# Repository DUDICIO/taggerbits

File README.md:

# taggerbits
An arduino based prototyping board with RFID and wifi capability on single PCB.

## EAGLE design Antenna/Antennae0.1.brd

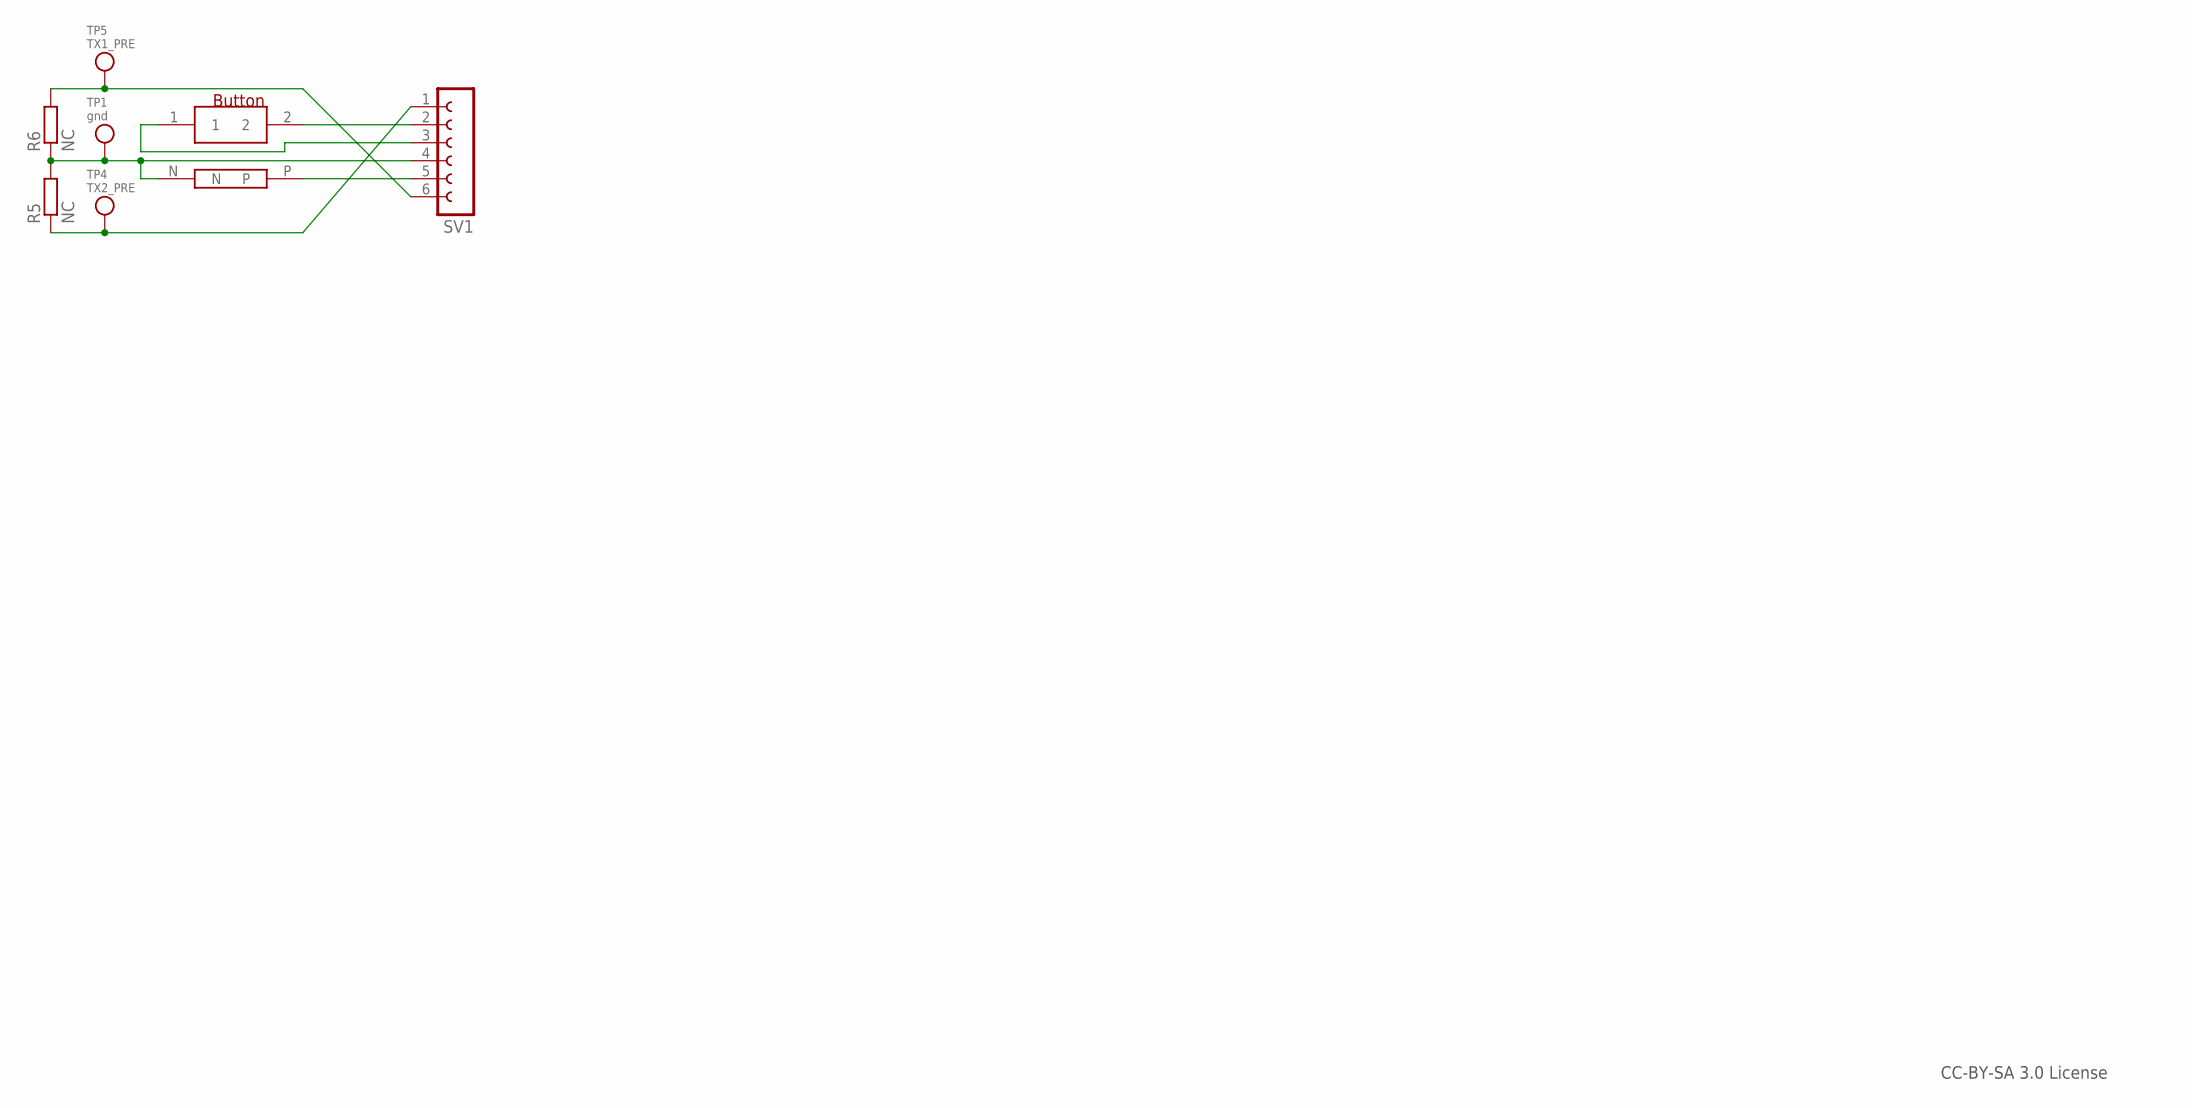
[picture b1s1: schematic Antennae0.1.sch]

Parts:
R5, R6: NC; R0201
SV1: FE06-1; FE06
TP1: gnd; TESTPOINT_PAD_2MM
TP4: TX2_PRE; TESTPOINT_PAD_2MM
TP5: TX1_PRE; TESTPOINT_PAD_2MM
U$1: BUTTON
U$2: LED(805)

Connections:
unnamed: SV1.2, U$1.2
unnamed: SV1.5, U$2.P
unnamed: R6.2, SV1.6, TP5.P$1
unnamed: R5.1, SV1.1, TP4.P$1
unnamed: R5.2, R6.1, SV1.4, TP1.P$1, U$2.N
VCC: SV1.3, U$1.1

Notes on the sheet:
CC-BY-SA 3.0 License

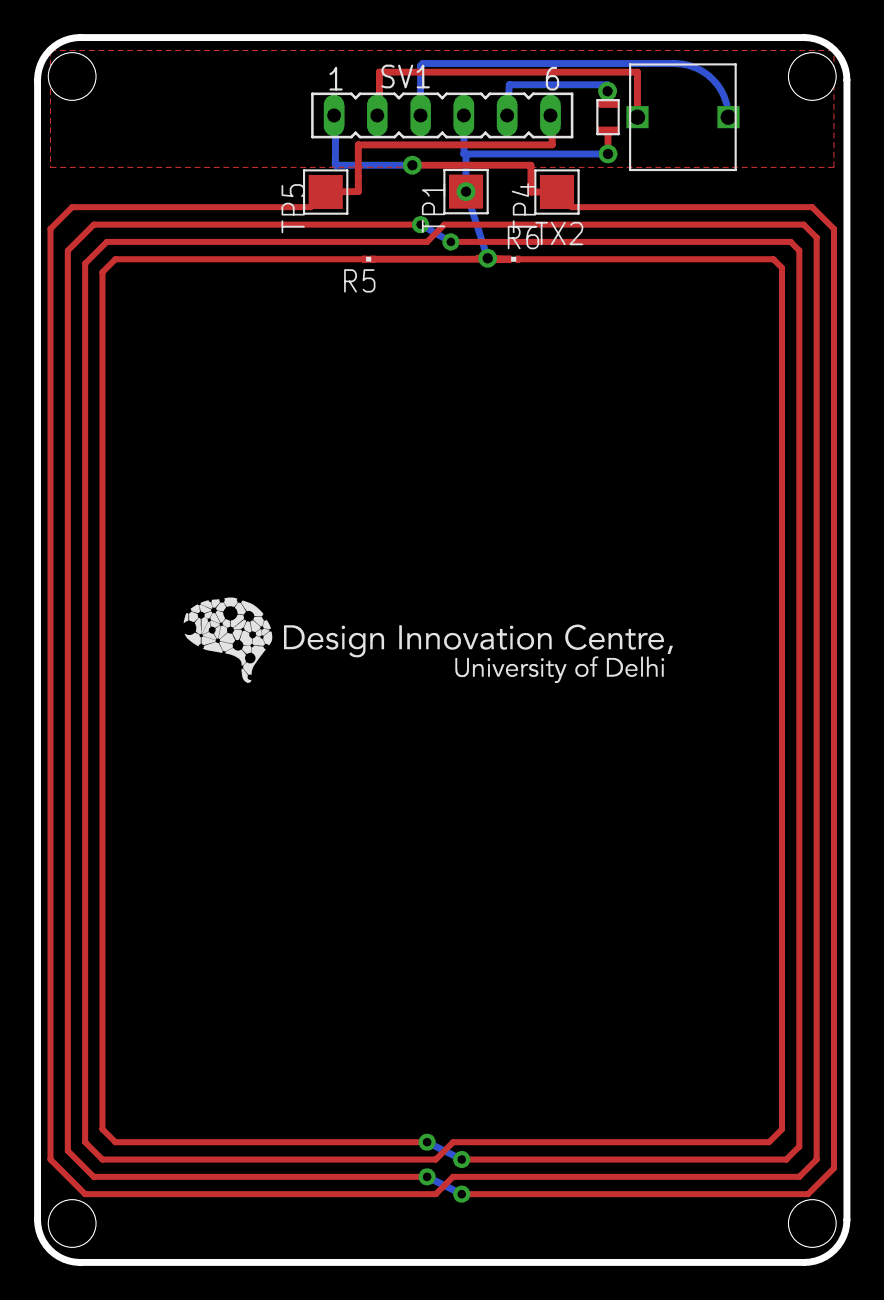
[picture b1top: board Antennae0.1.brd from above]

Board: 2 copper layers, 47.5 x 71.9 mm, 8 parts (0 on the bottom side), 6 nets.

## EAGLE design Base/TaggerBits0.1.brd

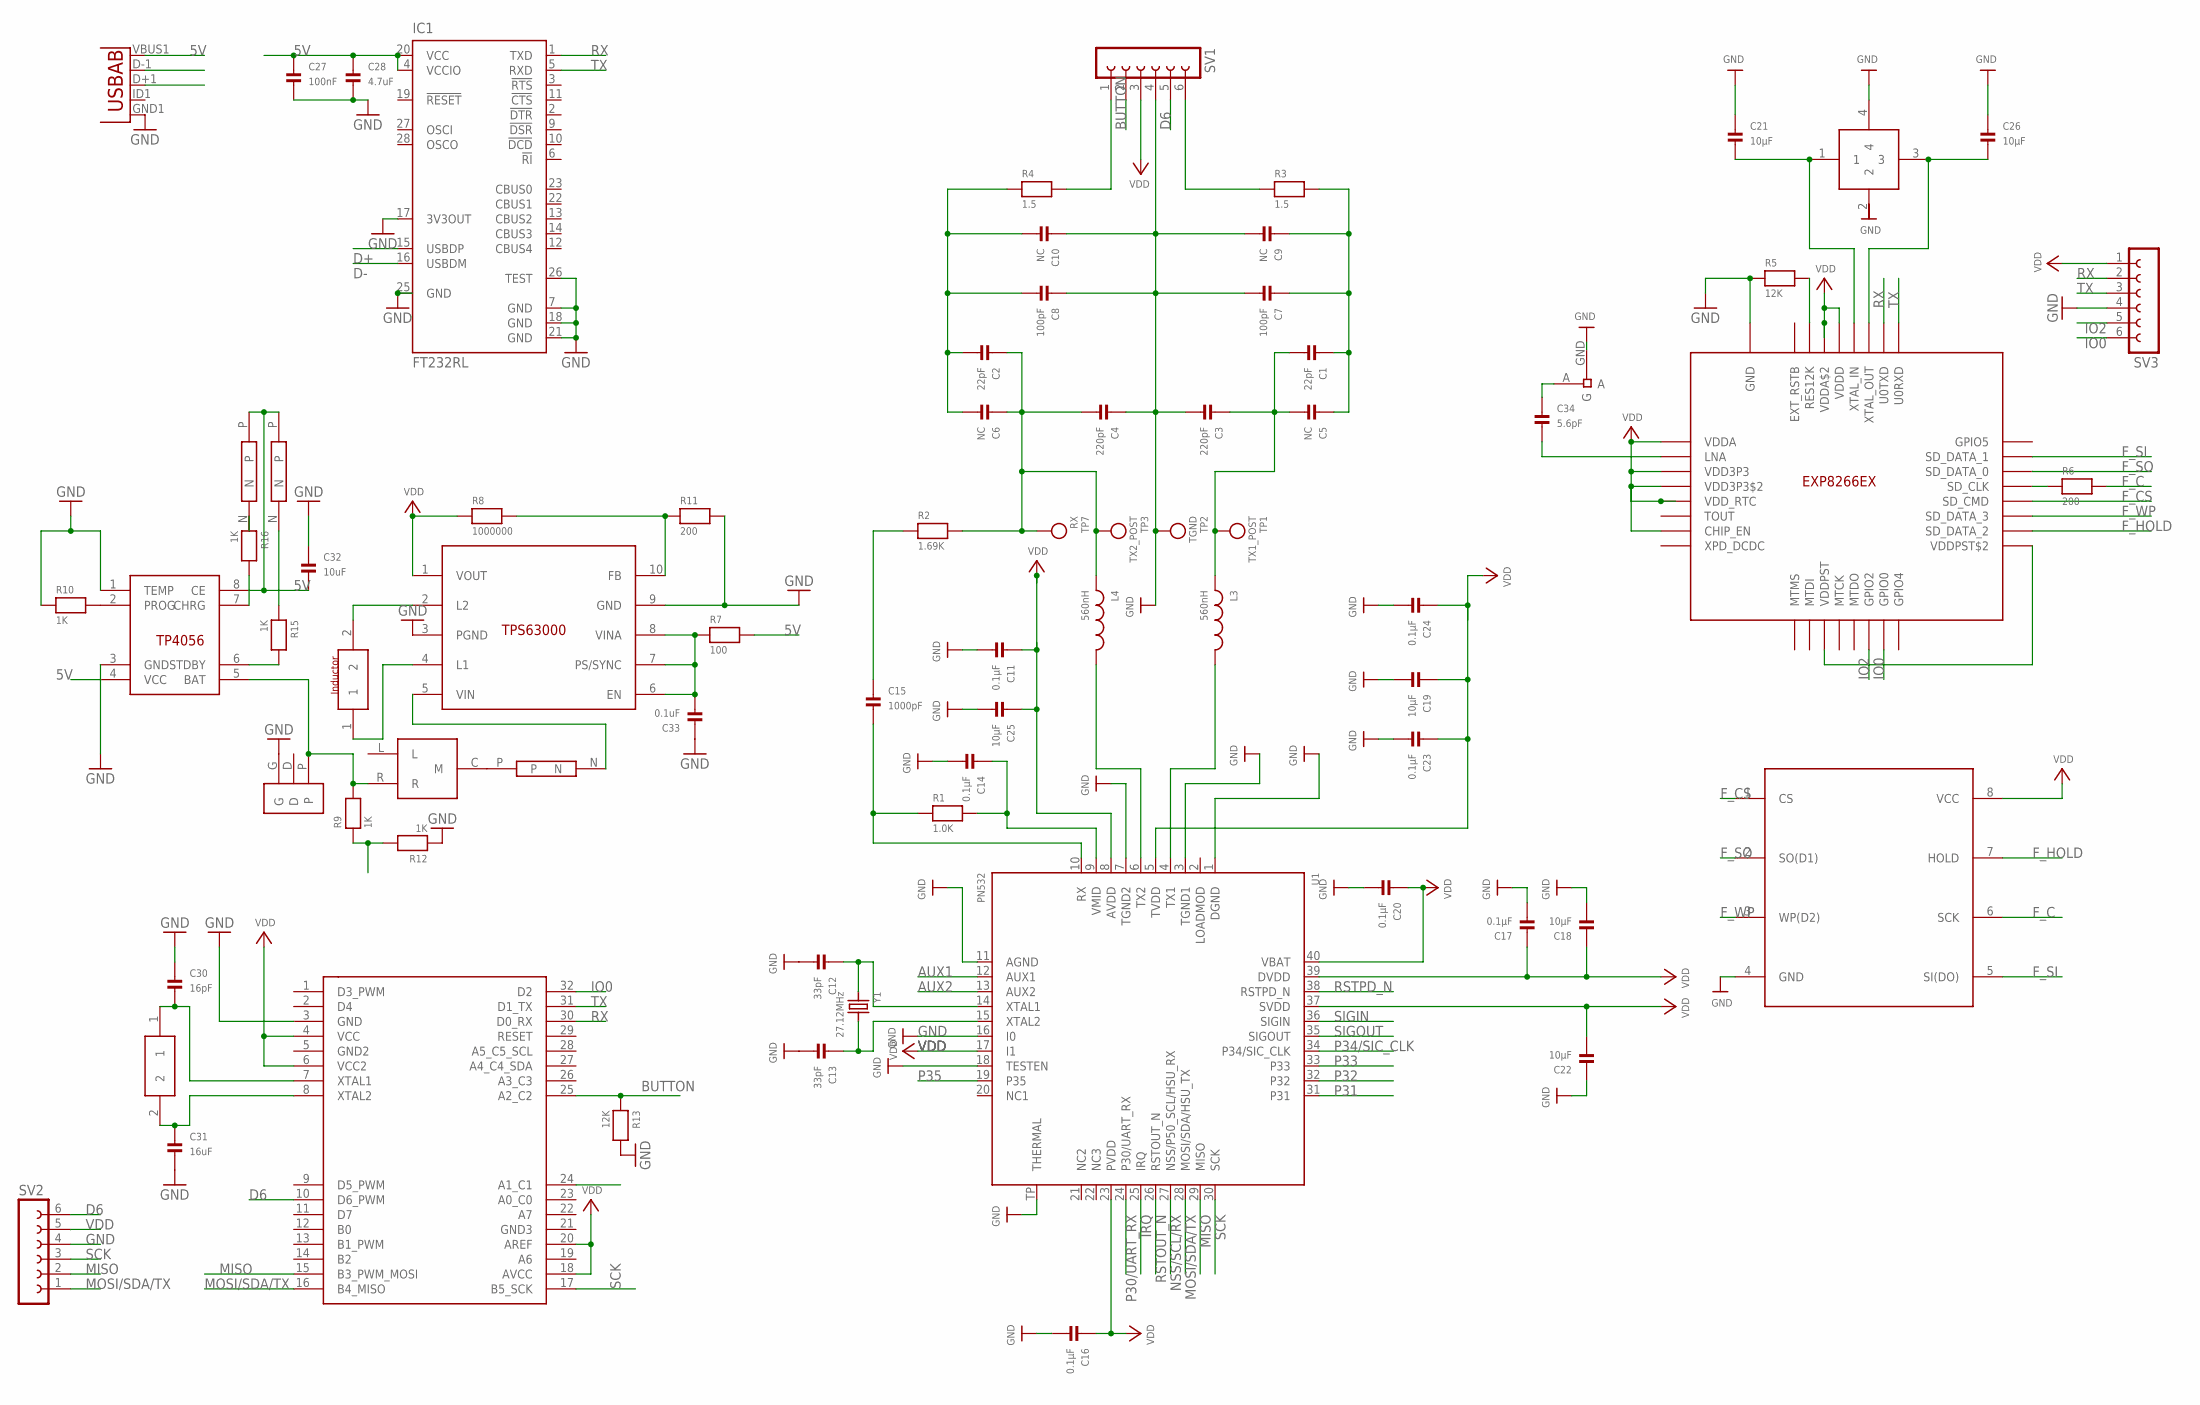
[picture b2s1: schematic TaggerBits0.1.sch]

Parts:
C1, C2: 22pF; 0805
C3, C4: 220pF; 0805
C5, C6, C9, C10: NC; 0805
C7, C8: 100pF; 0805
C11, C14, C16, C17, C20, C23, C24: 0.1µF; 0805
C12, C13: 33pF; 0805
C15: 1000pF; 0805
C18, C19, C21, C22, C25, C26: 10µF; 0805
C27: 100nF; 0805
C28: 4.7uF; 0805
C30: 16pF; 0805
C31: 16uF; 0805
C32: 10uF; 0805
C33: 0.1uF; 0805
C34: 5.6pF; 0805
GREEN: LED(805)
IC1: FT232RL; SSOP28
L3, L4: 560nH; 0805
LED: LED(805)
R1: 1.0K; 0805
R2: 1.69K; 0805
R3, R4: 1.5; 0805
R5, R13: 12K; 0805
R6, R11: 200; 0805
R7: 100; 0805
R8: 1000000; 0805
R9, R10, R12, R15, R16: 1K; 0805
RED: LED(805)
SV1, SV2, SV3: FE06-1; FE06
TP1: TX1_POST; TESTPOINT_PAD_2MM
TP2: TGND; TESTPOINT_PAD_2MM
TP3: TX2_POST; TESTPOINT_PAD_2MM
TP7: RX; TESTPOINT_PAD_2MM
U1: PN532; HVQFN40-6X6
U3: USB""; USB-MICRO-SMD
U4: ESP8266EX
U$3: FLASH; SO08
U$6: ATMEGA328TQFP; TQFP32-08
U$31: ANTENNAE
U$33: 26MHZ; T120
U$41: TP4056; SO08
U$42: CRYSTAL
U$44: TPS63000; SON10
U$47: SPDT
U$48: BCON
U$49: INDUCTOR
Y1: 27.12MHz; CRYSTAL_3.2X2.5

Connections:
5V: C27.1, C28.1, C32.2, GREEN.P, IC1.4 (VCCIO), IC1.20 (VCC), R7.2, RED.P, U3.VBUS1 (VBUS), U$41.4 (VCC), U$41.8 (CE)
AUX1: U1.12 (AUX1)
AUX2: U1.13 (AUX2)
BATTERYI: R9.1, R12.2, U$6.24 (A1_C1)
BUTTON: R13.1, SV1.2, U$6.25 (A2_C2)
D6: SV1.5, SV2.6, U$6.10 (D6_PWM)
D+: IC1.15 (USBDP), U3.D+1 (D+)
D-: IC1.16 (USBDM), U3.D-1 (D-)
F_C: R6.2, U$3.6 (SCK)
F_CS: U4.SD_CMD, U$3.1 (CS)
F_HOLD: U4.SD_DATA_2, U$3.7 (HOLD)
F_SI: U4.SD_DATA_1, U$3.5 (SI(DO))
F_SO: U4.SD_DATA_0, U$3.2 (SO(D1))
F_WP: U4.SD_DATA_3, U$3.3 (WP(D2))
GND: C3.2, C4.1, C7.2, C8.1, C9.2, C10.1, C11.2, C12.2, C13.2, C14.2, C16.2, C17.2, C18.2, C19.2, C20.2, C21.1, C22.1, C23.2, C24.2, C25.2, C26.1, C27.2, C28.2, C30.1, C31.2, C32.1, C33.1, IC1.7 (GND), IC1.17 (3V3OUT), IC1.18 (GND), IC1.21 (GND), IC1.25 (GND), IC1.26 (TEST), R5.1, R10.1, R11.2, R12.1, R13.2, SV1.4, SV2.4, SV3.4, TP2.P$1, U1.1 (DGND), U1.3 (TGND1), U1.7 (TGND2), U1.11 (AGND), U1.16 (I0), U1.18 (TESTEN), U1.TP (THERMAL), U3.GND1 (GND), U4.GND, U$3.4 (GND), U$6.3 (GND), U$31.GND (G), U$33.4, U$41.1 (TEMP), U$41.3 (GND), U$44.3 (PGND), U$44.9 (GND), U$48.G
IO0: SV3.6, U4.GPIO0, U$6.32 (D2)
IO2: SV3.5, U4.GPIO2
IRQ: U1.25 (IRQ)
MISO: SV2.2, U1.29 (MISO), U$6.15 (B3_PWM_MOSI)
MOSI/SDA/TX: SV2.1, U1.28 (MOSI/SDA/HSU_TX), U$6.16 (B4_MISO)
unnamed: L3.2, U1.4 (TX1)
unnamed: L4.2, U1.6 (TX2)
unnamed: C1.2, C3.1, C5.2, L3.1, TP1.P$1
unnamed: R3.1, SV1.6
unnamed: R4.2, SV1.1
unnamed: C34.2, U4.LNA
unnamed: C12.1, U1.14 (XTAL1), Y1.1
unnamed: C13.1, U1.15 (XTAL2), Y1.2
unnamed: C15.1, R2.1
unnamed: C14.1, R1.2, U1.9 (VMID)
unnamed: C15.2, R1.1, U1.10 (RX)
unnamed: C2.1, C4.2, C6.1, L4.1, R2.2, TP3.P$1, TP7.P$1
unnamed: LED.N, U$44.5 (VIN)
unnamed: C21.2, U4.XTAL_IN, U$33.1
unnamed: C30.2, U$6.7 (XTAL1), U$42.1
unnamed: C31.1, U$6.8 (XTAL2), U$42.2
unnamed: C33.2, R7.1, U$44.6 (EN), U$44.7 (PS/SYNC), U$44.8 (VINA)
unnamed: R8.2, R11.1, U$44.10 (FB)
unnamed: R5.2, U4.RES12K
unnamed: R6.1, U4.SD_CLK
unnamed: C26.2, U4.XTAL_OUT, U$33.3
unnamed: U4.VDDPST, U4.VDDPST$2
unnamed: R10.2, U$41.2 (PROG)
unnamed: R9.2, U$41.5 (BAT), U$47.R, U$48.P
unnamed: LED.P, U$47.C (M)
unnamed: U$44.4 (L1), U$49.1
unnamed: U$44.2 (L2), U$49.2
unnamed: C34.1, U$31.A
unnamed: R15.2, U$41.6 (STDBY)
unnamed: R16.2, U$41.7 (CHRG)
unnamed: GREEN.N, R15.1
unnamed: R16.1, RED.N
NSS/SCL/RX: U1.27 (NSS/P50_SCL/HSU_RX)
P30/UART_RX: U1.24 (P30/UART_RX)
P31: U1.31
P32: U1.32
P33: U1.33
P34/SIC_CLK: U1.34 (P34/SIC_CLK)
P35: U1.19 (P35)
RSTOUT_N: U1.26 (RSTOUT_N)
RSTPD_N: U1.38 (RSTPD_N)
RX: IC1.1 (TXD), SV3.2, U4.U0TXD, U$6.30 (D0_RX)
SCK: SV2.3, U1.30 (SCK), U$6.17 (B5_SCK)
SIGIN: U1.36 (SIGIN)
SIGOUT: U1.35 (SIGOUT)
TX: IC1.5 (RXD), SV3.3, U4.U0RXD, U$6.31 (D1_TX)
TX1_ANTENNA: C1.1, C5.1, C7.1, C9.1, R3.2
TX2_ANTENNA: C2.2, C6.2, C8.2, C10.2, R4.1
VDD: C11.1, C16.1, C17.1, C18.1, C19.1, C20.1, C22.2, C23.1, C24.1, C25.1, R8.1, SV1.3, SV2.5, SV3.1, U1.5 (TVDD), U1.8 (AVDD), U1.17 (I1), U1.23 (PVDD), U1.37 (SVDD), U1.39 (DVDD), U1.40 (VBAT), U4.CHIP_EN, U4.VDD3P3, U4.VDD3P3$2, U4.VDDA, U4.VDDA$2, U4.VDDD, U4.VDD_RTC, U$3.8 (VCC), U$6.4 (VCC), U$6.6 (VCC2), U$6.18 (AVCC), U$6.20 (AREF), U$44.1 (VOUT)

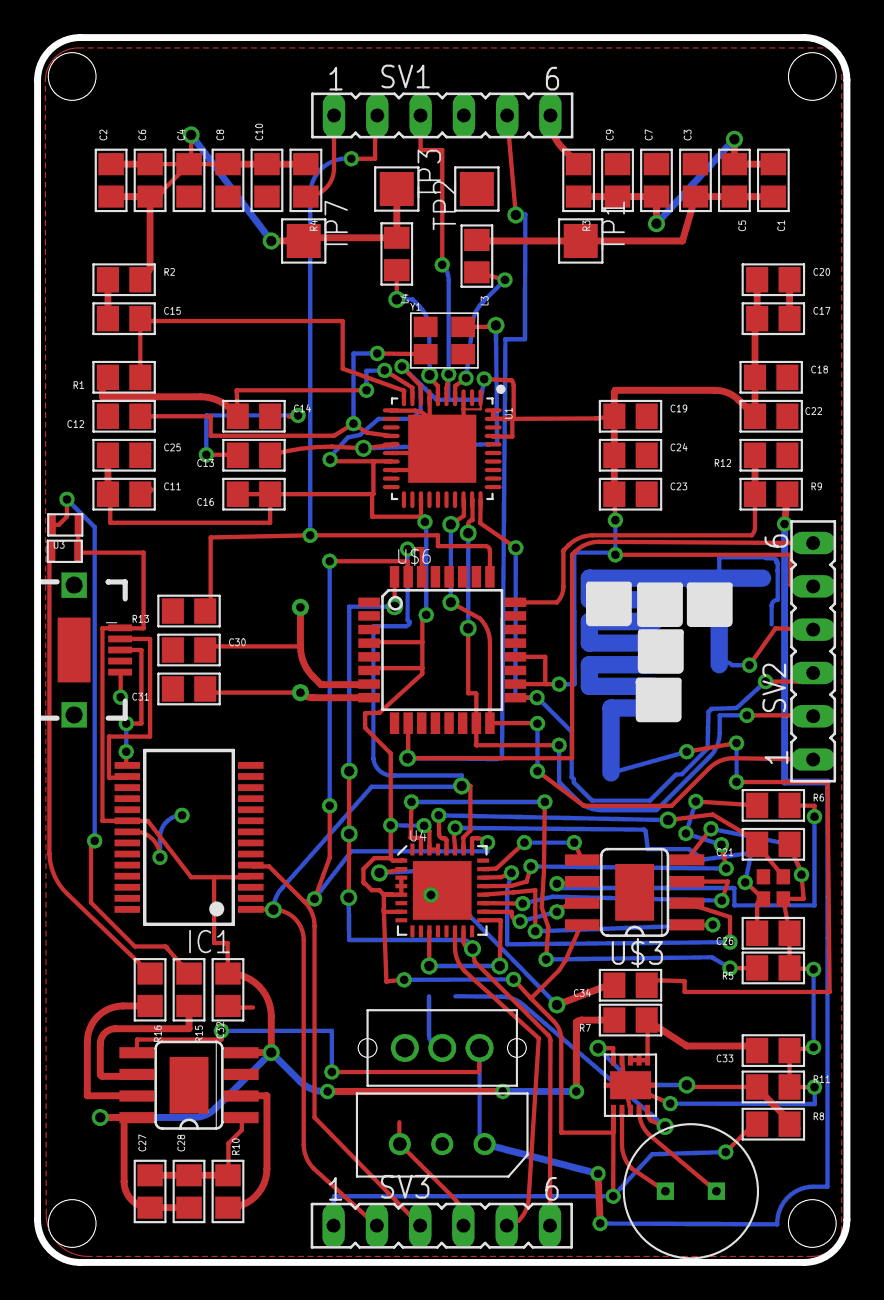
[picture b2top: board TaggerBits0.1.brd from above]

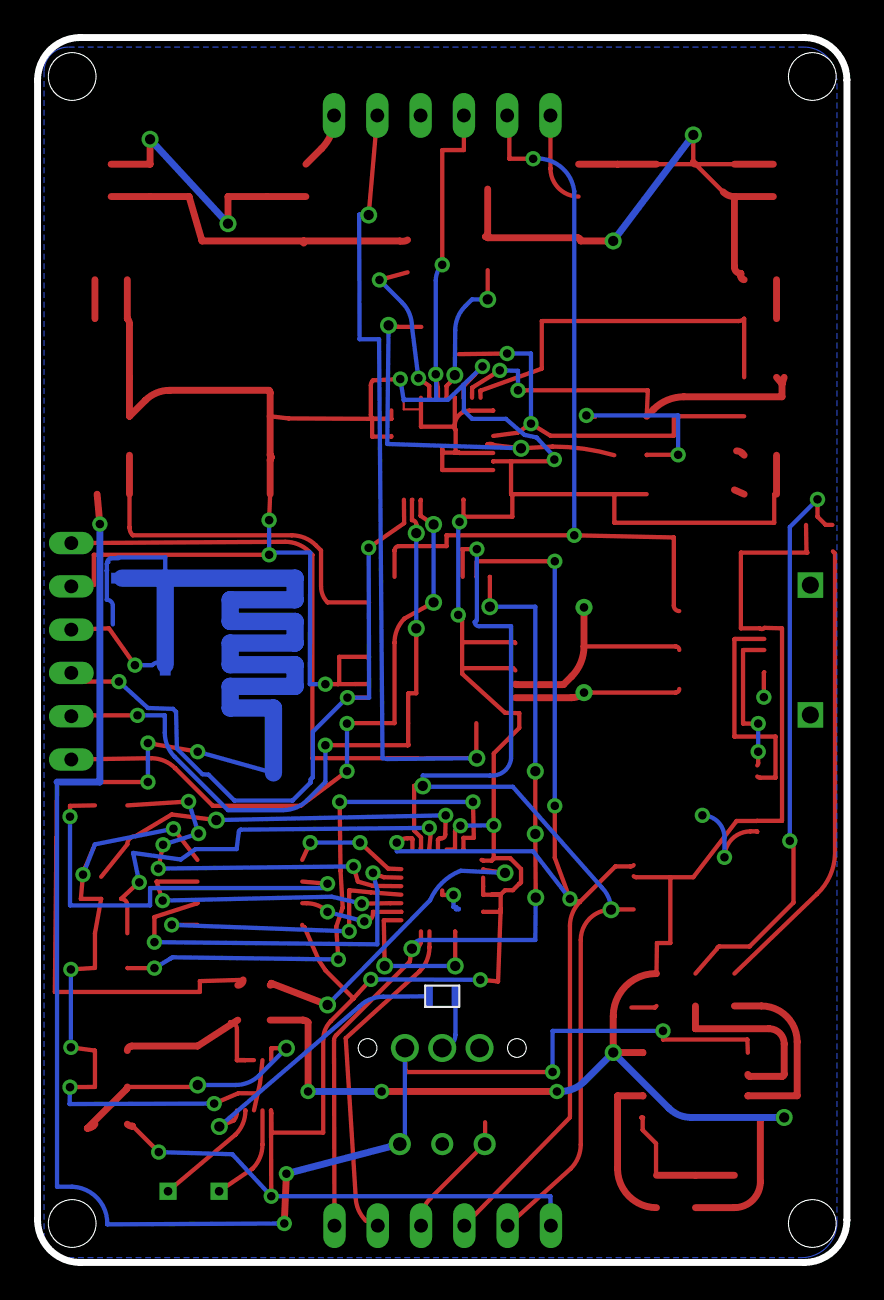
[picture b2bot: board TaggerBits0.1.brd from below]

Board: 2 copper layers, 47.5 x 71.9 mm, 75 parts (2 on the bottom side), 55 nets.

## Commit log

2016-06-23 Current board designs added
